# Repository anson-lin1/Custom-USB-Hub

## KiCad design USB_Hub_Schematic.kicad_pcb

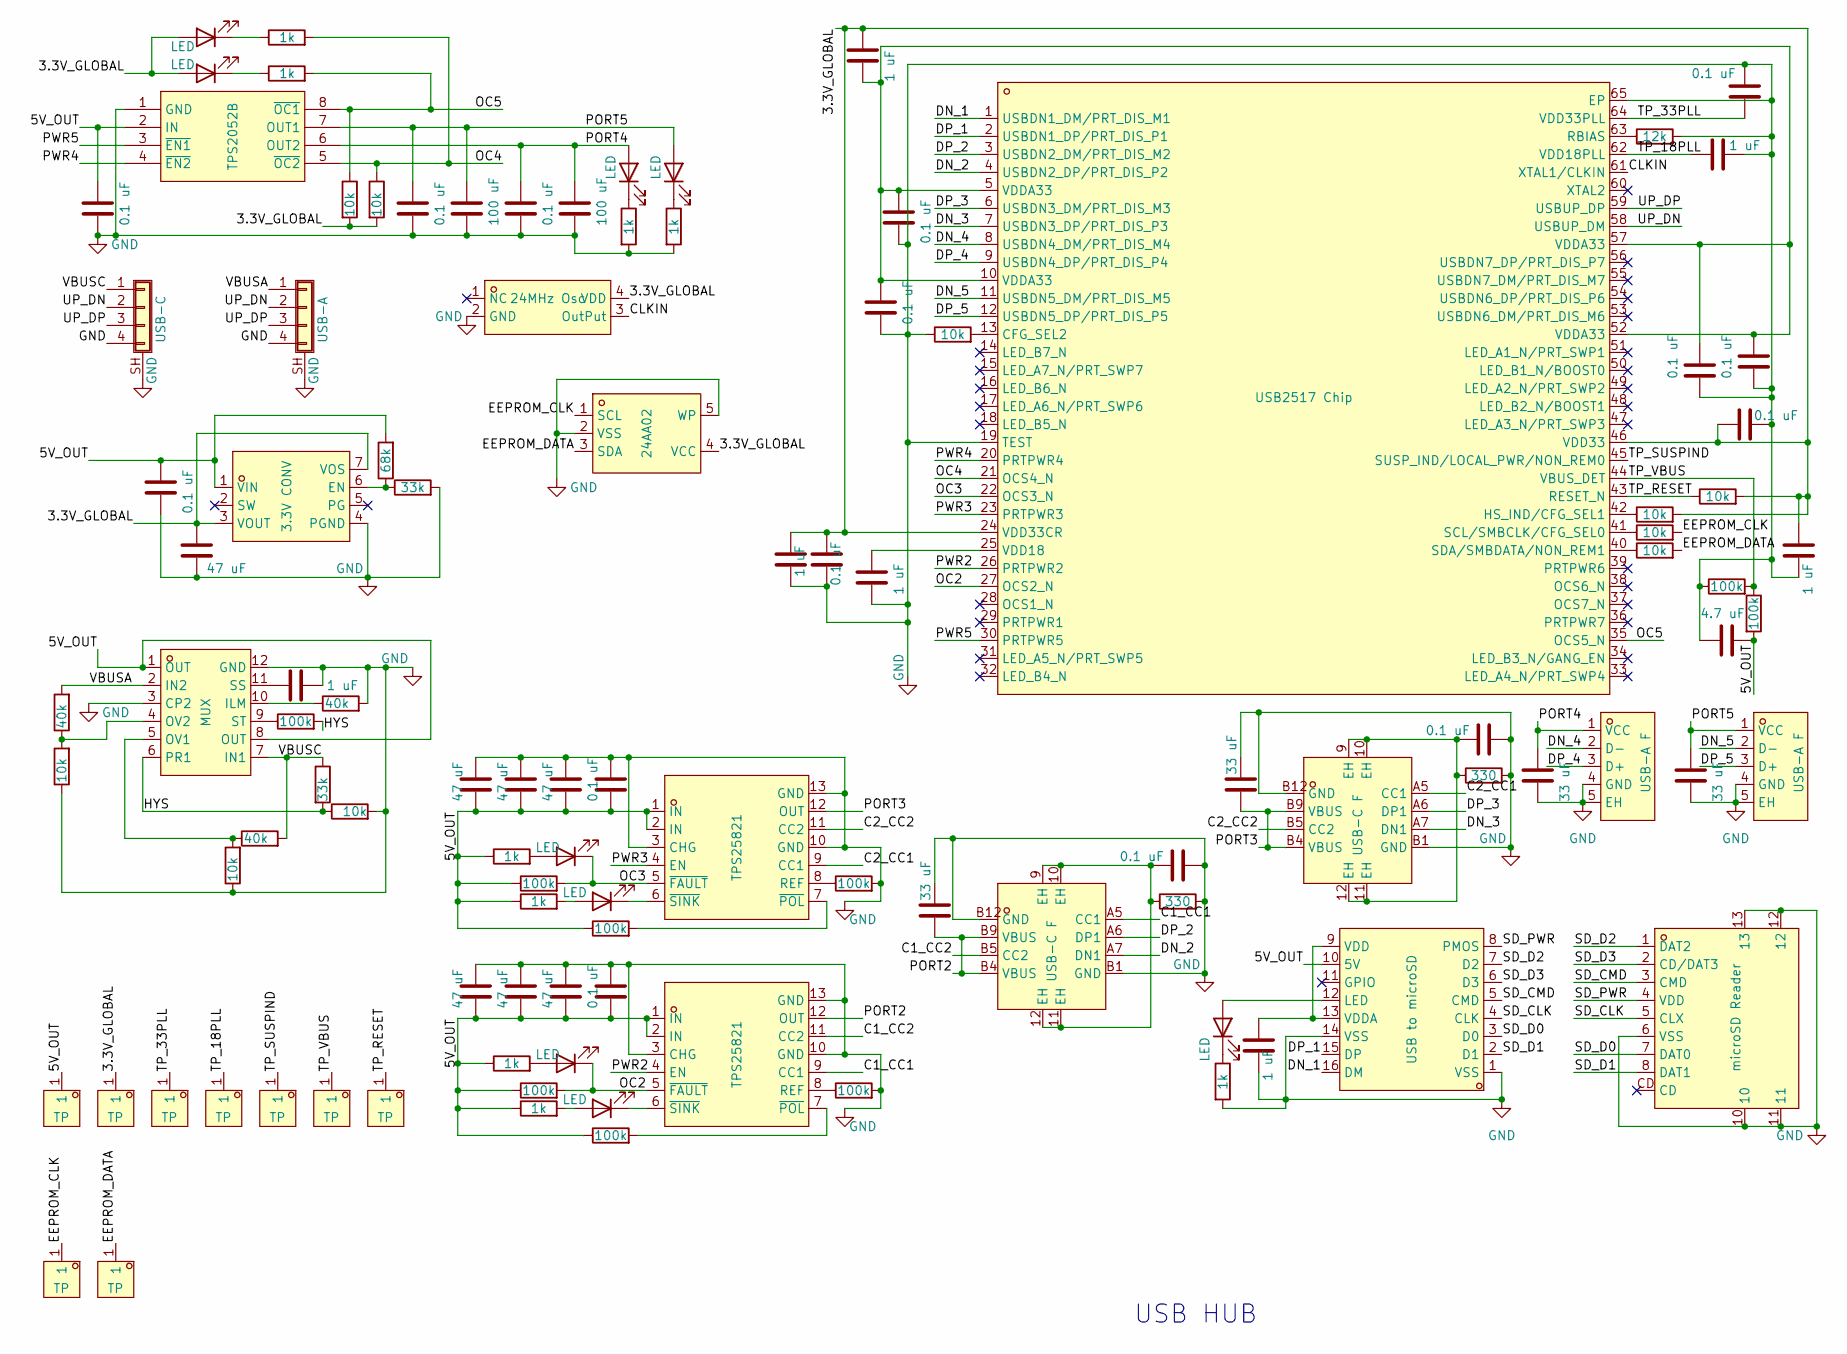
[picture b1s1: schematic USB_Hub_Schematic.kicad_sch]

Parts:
C1, C4, C5, C20, C22, C31, C35: 1 uF; C_0603_1608Metric; LCSC Part C15849
C2, C9, C18, C23, C24, C25, C26, C29, C32, C36, C37, C40, C41, C42, C44: 0.1 uF; C_0402_1005Metric; LCSC Part C1525
C3, C12, C13, C17, C33, C38, C39: 47 uF; C_0805_2012Metric; LCSC Part C16780
C19, C21, C30, C48: 33 uF; C_0805_2012Metric; LCSC Part C342635
C28: 4.7 uF; C_0603_1608Metric; LCSC Part C19666
C43, C45: 100 uF; C_1206_3216Metric; LCSC Part C15008
Card1: microSD Reader; TF-SMD_TF-PUSH; MPN TF PUSH; LCSC Part C393941
D2, D10, D13, D14, D15: LED; LED_0603_1608Metric; LCSC Part C2290
D11, D12, D16, D17: LED; LED_0603_1608Metric; LCSC Part C2286
J1: USB-C; SolderWire-0.1sqmm_1x04_P3.6mm_D0.4mm_OD1mm_Relief
J2: USB-A; SolderWire-0.1sqmm_1x04_P3.6mm_D0.4mm_OD1mm_Relief
R1, R2, R16, R34, R47, R49, R51, R54, R56: 100k; R_0603_1608Metric; LCSC Part C25803
R3, R4, R11, R13, R15, R27, R28, R29, R38, R41: 10k; R_0603_1608Metric; LCSC Part C177337
R5, R21, R23, R30, R31, R52, R53, R55, R57: 1k; R_0603_1608Metric; LCSC Part C177649
R6, R10: 33k; R_0603_1608Metric; LCSC Part C4216
R7: 68k; R_0603_1608Metric; LCSC Part C22356449
R9, R12, R14: 40k; R_0603_1608Metric; LCSC Part C861392
R17: 12k; R_0603_1608Metric; LCSC Part C22790
R32, R33: 330; R_0603_1608Metric; LCSC Part C23138
U1: USB2517 Chip; QFN-64_L9.0-W9.0-P0.50-BL-EP4.8; MPN USB2517-JZX; LCSC Part C1521556
U2: 3.3V CONV; QFN-7_L4.0-W3.3_TPSM863257RDXR; MPN TPSM863253RDXR; LCSC Part C30051679
U3: MUX; VQFN-HR-12_L2.5-W2.0-P0.50-BL; MPN TPS2121RUXR; LCSC Part C485916
U4: USB to microSD; SSOP-16_L4.9-W3.9-P0.64-LS6.0-BL; MPN GL823K-HCY04; LCSC Part C284879
U5: 24AA02; SOT-23-5_L2.9-W1.6-P0.95-LS2.8-BL-3; MPN 24AA02T-I/OT; LCSC Part C478090
U7: TPS2052B; SOIC-8_L4.9-W3.9-P1.27-LS6.0-BL; MPN TPS2052BD; LCSC Part C131918
U9, U10, U11, U12, U13, U14, U15, U18, U19: TP; TEST-SMD_L2.7-W1.0; MPN 5015; LCSC Part C2906768
U16, U17: TPS25821; WSON-12_L3.0-W2.0-P0.5-BL-EP; MPN TPS25821DSSR; LCSC Part C2861545
USB3, USB4: USB-C F; USB-C-SMD_MC-403L68-Z20; MPN MC-403L68-Z20; LCSC Part C47326497
USB6, USB7: USB-A F; USB-A-TH_USB-226-BRY; MPN USB-226-BRY; LCSC Part C720523
X3: 24MHz Osc; OSC-SMD_4P-L3.2-W2.5-CJ13-320001210A20; MPN OW2EL89CENUXFMYLC-24M; LCSC Part C22434893

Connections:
/3.3V_GLOBAL: C3.1, C5.1, C31.1, C32.1, C35.1, C36.1, D16.2 (A), D17.2 (A), R3.2, R4.2, R27.2, R41.2, U1.24 (VDD33CR), U1.46 (VDD33), U2.3 (VOUT), U2.7 (VOS), U5.4 (VCC), U10.1 (1_1), X3.4 (VDD)
/5V_OUT: C2.1, C12.2, C13.2, C17.2, C28.1, C33.2, C37.2, C38.2, C39.2, C40.2, C41.1, R7.2, R23.1, R34.2, R49.1, R51.1, R52.1, R53.1, R54.1, R55.1, R56.1, U2.1 (VIN), U3.1 (OUT), U3.8 (OUT), U4.10 (5V), U7.2 (IN), U9.1 (1_1), U16.1 (IN), U16.2 (IN), U17.1 (IN), U17.2 (IN)
/C1_CC1: U16.9 (CC1), USB3.A5 (CC1)
/C1_CC2: U16.11 (CC2), USB3.B5 (CC2)
/C2_CC1: U17.9 (CC1), USB4.A5 (CC1)
/C2_CC2: U17.11 (CC2), USB4.B5 (CC2)
/CLKIN: U1.61 (XTAL1/CLKIN), X3.3 (OutPut)
/DN_1: U1.1 (USBDN1_DM/PRT_DIS_M1), U4.16 (DM)
/DN_2: U1.4 (USBDN2_DP/PRT_DIS_P2), USB3.A7 (DN1)
/DN_3: U1.7 (USBDN3_DP/PRT_DIS_P3), USB4.A7 (DN1)
/DN_4: U1.8 (USBDN4_DM/PRT_DIS_M4), USB6.2 (D-)
/DN_5: U1.11 (USBDN5_DM/PRT_DIS_M5), USB7.2 (D-)
/DP_1: U1.2 (USBDN1_DP/PRT_DIS_P1), U4.15 (DP)
/DP_2: U1.3 (USBDN2_DM/PRT_DIS_M2), USB3.A6 (DP1)
/DP_3: U1.6 (USBDN3_DM/PRT_DIS_M3), USB4.A6 (DP1)
/DP_4: U1.9 (USBDN4_DP/PRT_DIS_P4), USB6.3 (D+)
/DP_5: U1.12 (USBDN5_DP/PRT_DIS_P5), USB7.3 (D+)
/EEPROM_CLK: R28.2, U5.1 (SCL), U18.1 (1_1)
/EEPROM_DATA: R38.2, U5.3 (SDA), U19.1 (1_1)
/HYS: R10.2, R11.1, R16.2, U3.6 (PR1)
/OC2: D11.1 (K), R51.2, U1.27 (OCS2_N), U16.5 (~FAULT)
/OC3: D12.1 (K), R54.2, U1.22 (OCS3_N), U17.5 (~FAULT)
/OC4: R4.1, R30.2, U1.21 (OCS4_N), U7.5 (~OC2)
/OC5: R3.1, R31.2, U1.35 (OCS5_N), U7.8 (~OC1)
/PORT2: C19.2, U16.12 (OUT), USB3.B4 (VBUS), USB3.B9 (VBUS)
/PORT3: C21.2, U17.12 (OUT), USB4.B4 (VBUS), USB4.B9 (VBUS)
/PORT4: C30.1, C44.1, C45.1, D14.2 (A), U7.6 (OUT2), USB6.1 (VCC)
/PORT5: C42.1, C43.1, C48.1, D15.2 (A), U7.7 (OUT1), USB7.1 (VCC)
/PWR2: U1.26 (PRTPWR2), U16.4 (EN)
/PWR3: U1.23 (PRTPWR3), U17.4 (EN)
/PWR4: U1.20 (PRTPWR4), U7.4 (~EN2)
/PWR5: U1.30 (PRTPWR5), U7.3 (~EN1)
/SD_CLK: Card1.5 (CLX), U4.4 (CLK)
/SD_CMD: Card1.3 (CMD), U4.5 (CMD)
/SD_D0: Card1.7 (DAT0), U4.3 (D0)
/SD_D1: Card1.8 (DAT1), U4.2 (D1)
/SD_D2: Card1.1 (DAT2), U4.7 (D2)
/SD_D3: Card1.2 (CD/DAT3), U4.6 (D3)
/SD_PWR: Card1.4 (VDD), U4.8 (PMOS)
/TP_18PLL: C22.1, U1.62 (VDD18PLL), U12.1 (1_1)
/TP_33PLL: C24.2, U1.64 (VDD33PLL), U11.1 (1_1)
/TP_RESET: R41.1, U1.43 (RESET_N), U15.1 (1_1)
/TP_SUSPIND: U1.45 (SUSP_IND/LOCAL_PWR/NON_REM0), U13.1 (1_1)
/TP_VBUS: R34.1, R47.2, U1.44 (VBUS_DET), U14.1 (1_1)
/UP_DN: J1.2, J2.2, U1.58 (USBUP_DM)
/UP_DP: J1.3, J2.3, U1.59 (USBUP_DP)
/VBUSA: J2.1, R14.2, U3.2 (IN2)
/VBUSC: J1.1, R10.1, R12.2, U3.7 (IN1)
GND: C1.2, C2.2, C3.2, C4.2, C5.2, C9.2, C12.1, C13.1, C17.1, C18.2, C19.1, C20.2, C21.1, C22.2, C23.2, C24.1, C25.2, C26.2, C28.2, C29.2, C30.2, C32.2, C33.1, C35.2, C36.2, C37.1, C38.1, C39.1, C40.1, C41.2, C42.2, C43.2, C44.2, C45.2, C48.2, Card1.6 (VSS), Card1.10, Card1.11, Card1.12, Card1.13, J1.4, J1.SH (Shield), J2.4, J2.SH (Shield), R1.2, R2.2, R5.2, R6.2, R9.2, R11.2, R13.1, R15.1, R17.2, R21.2, R29.1, R32.2, R33.2, R47.1, R57.2, U1.19 (TEST), U1.65 (EP), U2.4 (PGND), U3.3 (CP2), U3.12 (GND), U4.1 (VSS), U4.14 (VSS), U5.2 (VSS), U5.5 (WP), U7.1 (GND), U16.3 (CHG), U16.10 (GND), U16.13 (GND), U17.3 (CHG), U17.10 (GND), U17.13 (GND), USB3.B1 (GND), USB3.B12 (GND), USB4.B1 (GND), USB4.B12 (GND), USB6.4 (GND), USB6.5 (EH), USB7.4 (GND), USB7.5 (EH), X3.2 (GND)
unnamed: C18.1, R32.1, USB3.9 (EH), USB3.10 (EH), USB3.11 (EH), USB3.12 (EH)
unnamed: C9.1, C23.1, C25.1, C29.1, C31.2, U1.5 (VDDA33), U1.10 (VDDA33), U1.52 (VDDA33), U1.57 (VDDA33)
unnamed: C26.1, R33.1, USB4.9 (EH), USB4.10 (EH), USB4.11 (EH), USB4.12 (EH)
unnamed: D2.2 (A), U4.12 (LED)
unnamed: D2.1 (K), R5.1
unnamed: D10.2 (A), R23.2
unnamed: D10.1 (K), U16.6 (~SINK)
unnamed: D11.2 (A), R52.2
unnamed: D12.2 (A), R53.2
unnamed: D13.2 (A), R55.2
unnamed: D13.1 (K), U17.6 (~SINK)
unnamed: D14.1 (K), R21.1
unnamed: D15.1 (K), R57.1
unnamed: D16.1 (K), R31.1
unnamed: D17.1 (K), R30.1
unnamed: R29.2, U1.13 (CFG_SEL2)
unnamed: R27.1, U1.42 (HS_IND/CFG_SEL1)
unnamed: R17.1, U1.63 (RBIAS)
unnamed: R28.1, U1.41 (SCL/SMBCLK/CFG_SEL0)
unnamed: R38.1, U1.40 (SDA/SMBDATA/NON_REM1)
unnamed: C20.1, U1.25 (VDD18)
unnamed: R6.1, R7.1, U2.6 (EN)
unnamed: R9.1, U3.10 (ILM)
unnamed: R12.1, R13.2, U3.5 (OV1)
unnamed: R14.1, R15.2, U3.4 (OV2)
unnamed: C4.1, U3.11 (SS)
unnamed: R16.1, U3.9 (ST)
unnamed: C1.1, U4.9 (VDD), U4.13 (VDDA)
unnamed: R1.1, U16.8 (REF)
unnamed: R49.2, U16.7 (~POL)
unnamed: R2.1, U17.8 (REF)
unnamed: R56.2, U17.7 (~POL)

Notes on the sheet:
USB HUB

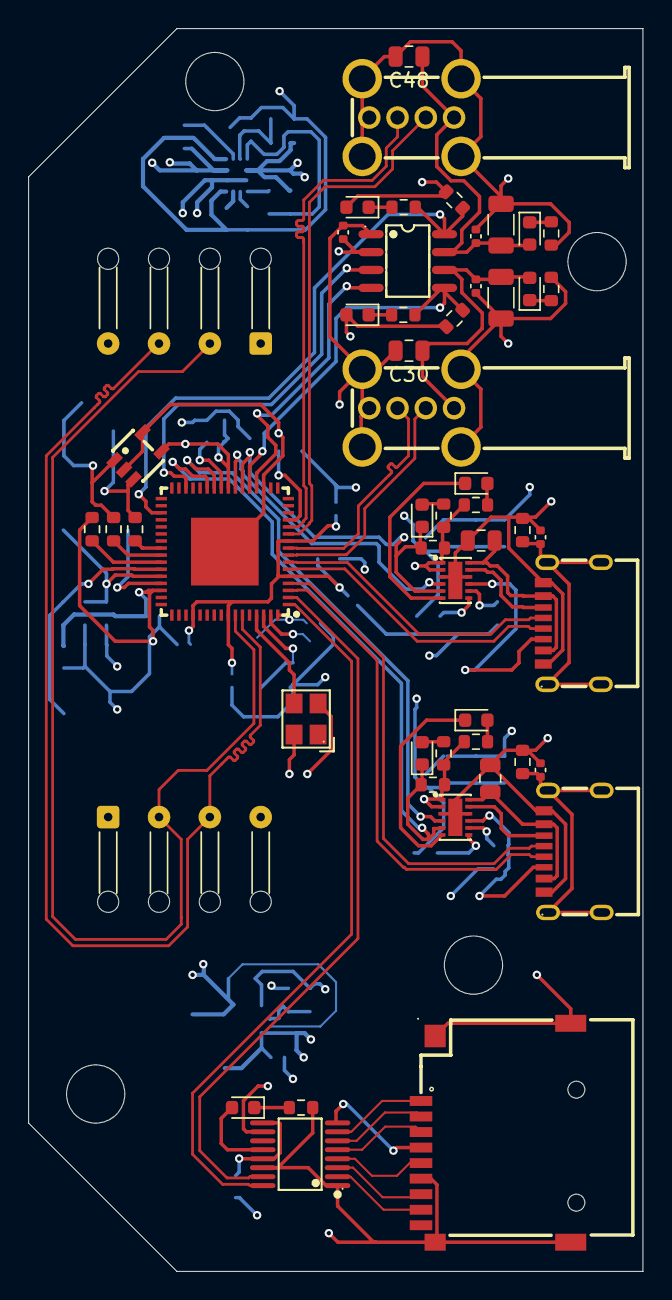
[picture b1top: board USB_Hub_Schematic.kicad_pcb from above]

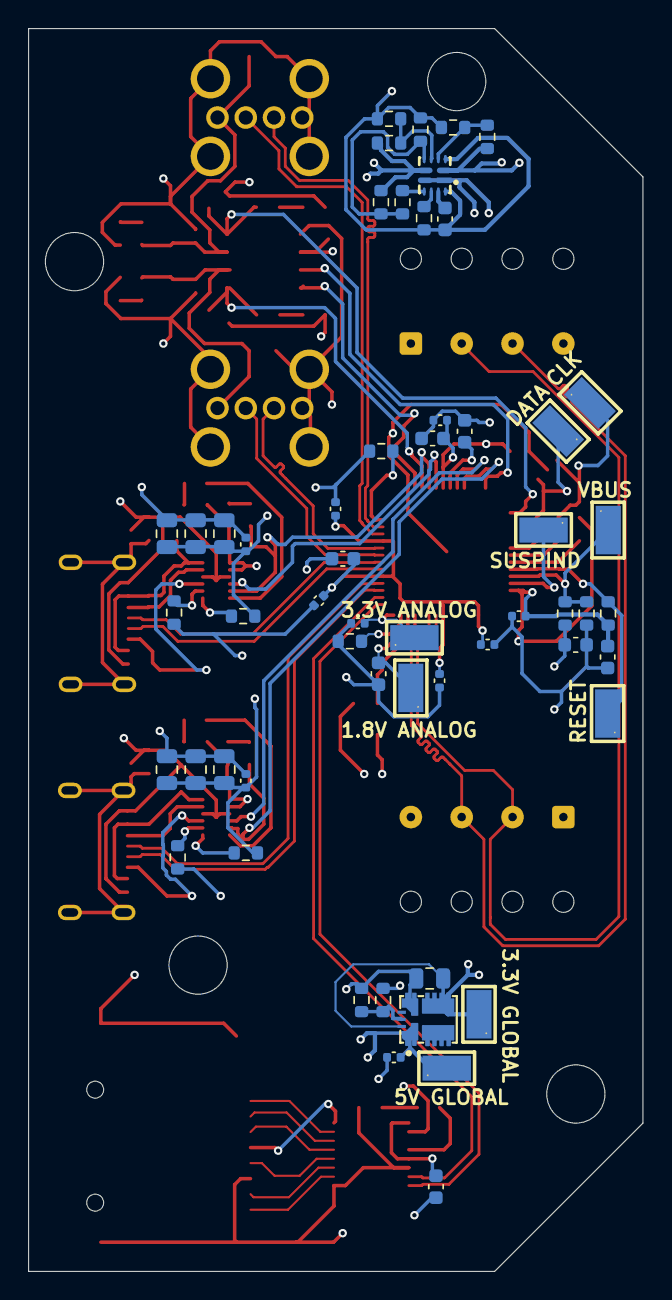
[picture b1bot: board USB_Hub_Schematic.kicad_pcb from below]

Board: 4 copper layers, 43.5 x 88.0 mm, 107 parts (55 on the bottom side), 81 nets.

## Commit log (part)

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2026-06-24 Stuff
2026-06-24 Add PCB scripts submodule
2026-06-24 Updating scripts
2026-06-24 Started KiCAD
    Put all relevant ports/chips into KiCAD
2026-06-25 New parts
2026-06-26 KiCAD Work
2026-06-27 Continued schematics
2026-06-28 New schematic
